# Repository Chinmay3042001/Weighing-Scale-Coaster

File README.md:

# Weighing Scale Coaster

A precision coffee scale built around the HX711 load cell amplifier, optimized for responsiveness and stability. Designed for baristas, tinkerers, and embedded engineers who care about both performance and personality.

## Features
• 	HX711-based load cell interface with high-resolution weight readings

• 	Reference-inspired filtering pipeline adapted from Analog Devices' weigh scale design

• 	OLED display with expressive dome-shaped eyes and smile animation

• 	Timer with short press toggle and long press reset

• 	Flicker-free weight display using hysteresis and trimmed averaging

• 	Designed for both Raspberry Pi Pico W and Seeed Studio XIAO ESP32-C6

## Hardware Overview
### Components
• 	HX711 Load Cell Amplifier

• 	5 kg Load Cell

• 	SSD1306 OLED Display (128×32)

• 	Two momentary push buttons (Tare + Timer) . To be replaced with capacitive touch 

• 	Microcontroller: Raspberry Pi Pico W or Seeed Studio XIAO ESP32-C6

## Wiring Table

| Pin on OLED       | Pin on HX711 | Pin on Pico W | Pin on XIAO ESP32-C6 |
|---------------|--------------|----------------|----------------------|
| VCC           | VCC          | 3.3V           | 3.3V                 |
| GND           | GND          | GND            | GND                  |    
| Data (DT)     | DT           | GPIO 16        | GPIO 10              |
| Clock (SCK)   | SCK          | GPIO 17        | GPIO 11              |
| OLED SDA      | SDA          | GPIO 4         | GPIO 4               |    
| OLED SCL      | SCL          | GPIO 5         | GPIO 5               |
| Tare Button   | -            | GPIO 18        | GPIO 6               |
| Timer Button  | -            | GPIO 19        | GPIO 7               |

## Load Cell Algorithm
This project adapts the signal processing architecture from Analog Devices' weigh scale reference design to the HX711.
Filtering Pipeline

• 	Trimmed Moving Average: Removes min/max outliers from a rolling window to suppress noise while preserving step response.

• 	Step Detection: Detects real weight changes using dual-threshold logic and pre-fills the filter buffer to skip lag.

• 	Display Hysteresis: Prevents flicker by suppressing small changes below a threshold.

### Why It Works
• 	HX711 is a 24-bit sigma-delta ADC with built-in gain and ratiometric measurement.

• 	Filtering compensates for its limited noise-free resolution and slow sample rate.

• 	The result: smooth, stable, and responsive weight readings even with low-cost hardware.

## User Interaction

OLED shows timer and weight. Startup animation includes blinking eyes and a smile. A Hall effect sensor to be integrated for a lid-activated deep sleep and wake mode.

Future Improvements
• 	Calibration helper script for computing 

• 	BLE or Wi-Fi integration for remote brew tracking

• 	Capacitive touch buttons

Credits
Built by Maurice D'Moss, mechanical product design engineer with a passion for coffee and embedded systems.
Filtering architecture inspired by Analog Devices' weigh scale reference design.

## License

This project is licensed under the [Creative Commons Attribution-NonCommercial 4.0 International License](https://creativecommons.org/licenses/by-nc/4.0/).

You are free to use, modify, and share this project for personal and educational purposes.  
Commercial use is not permitted without explicit permission from the author.

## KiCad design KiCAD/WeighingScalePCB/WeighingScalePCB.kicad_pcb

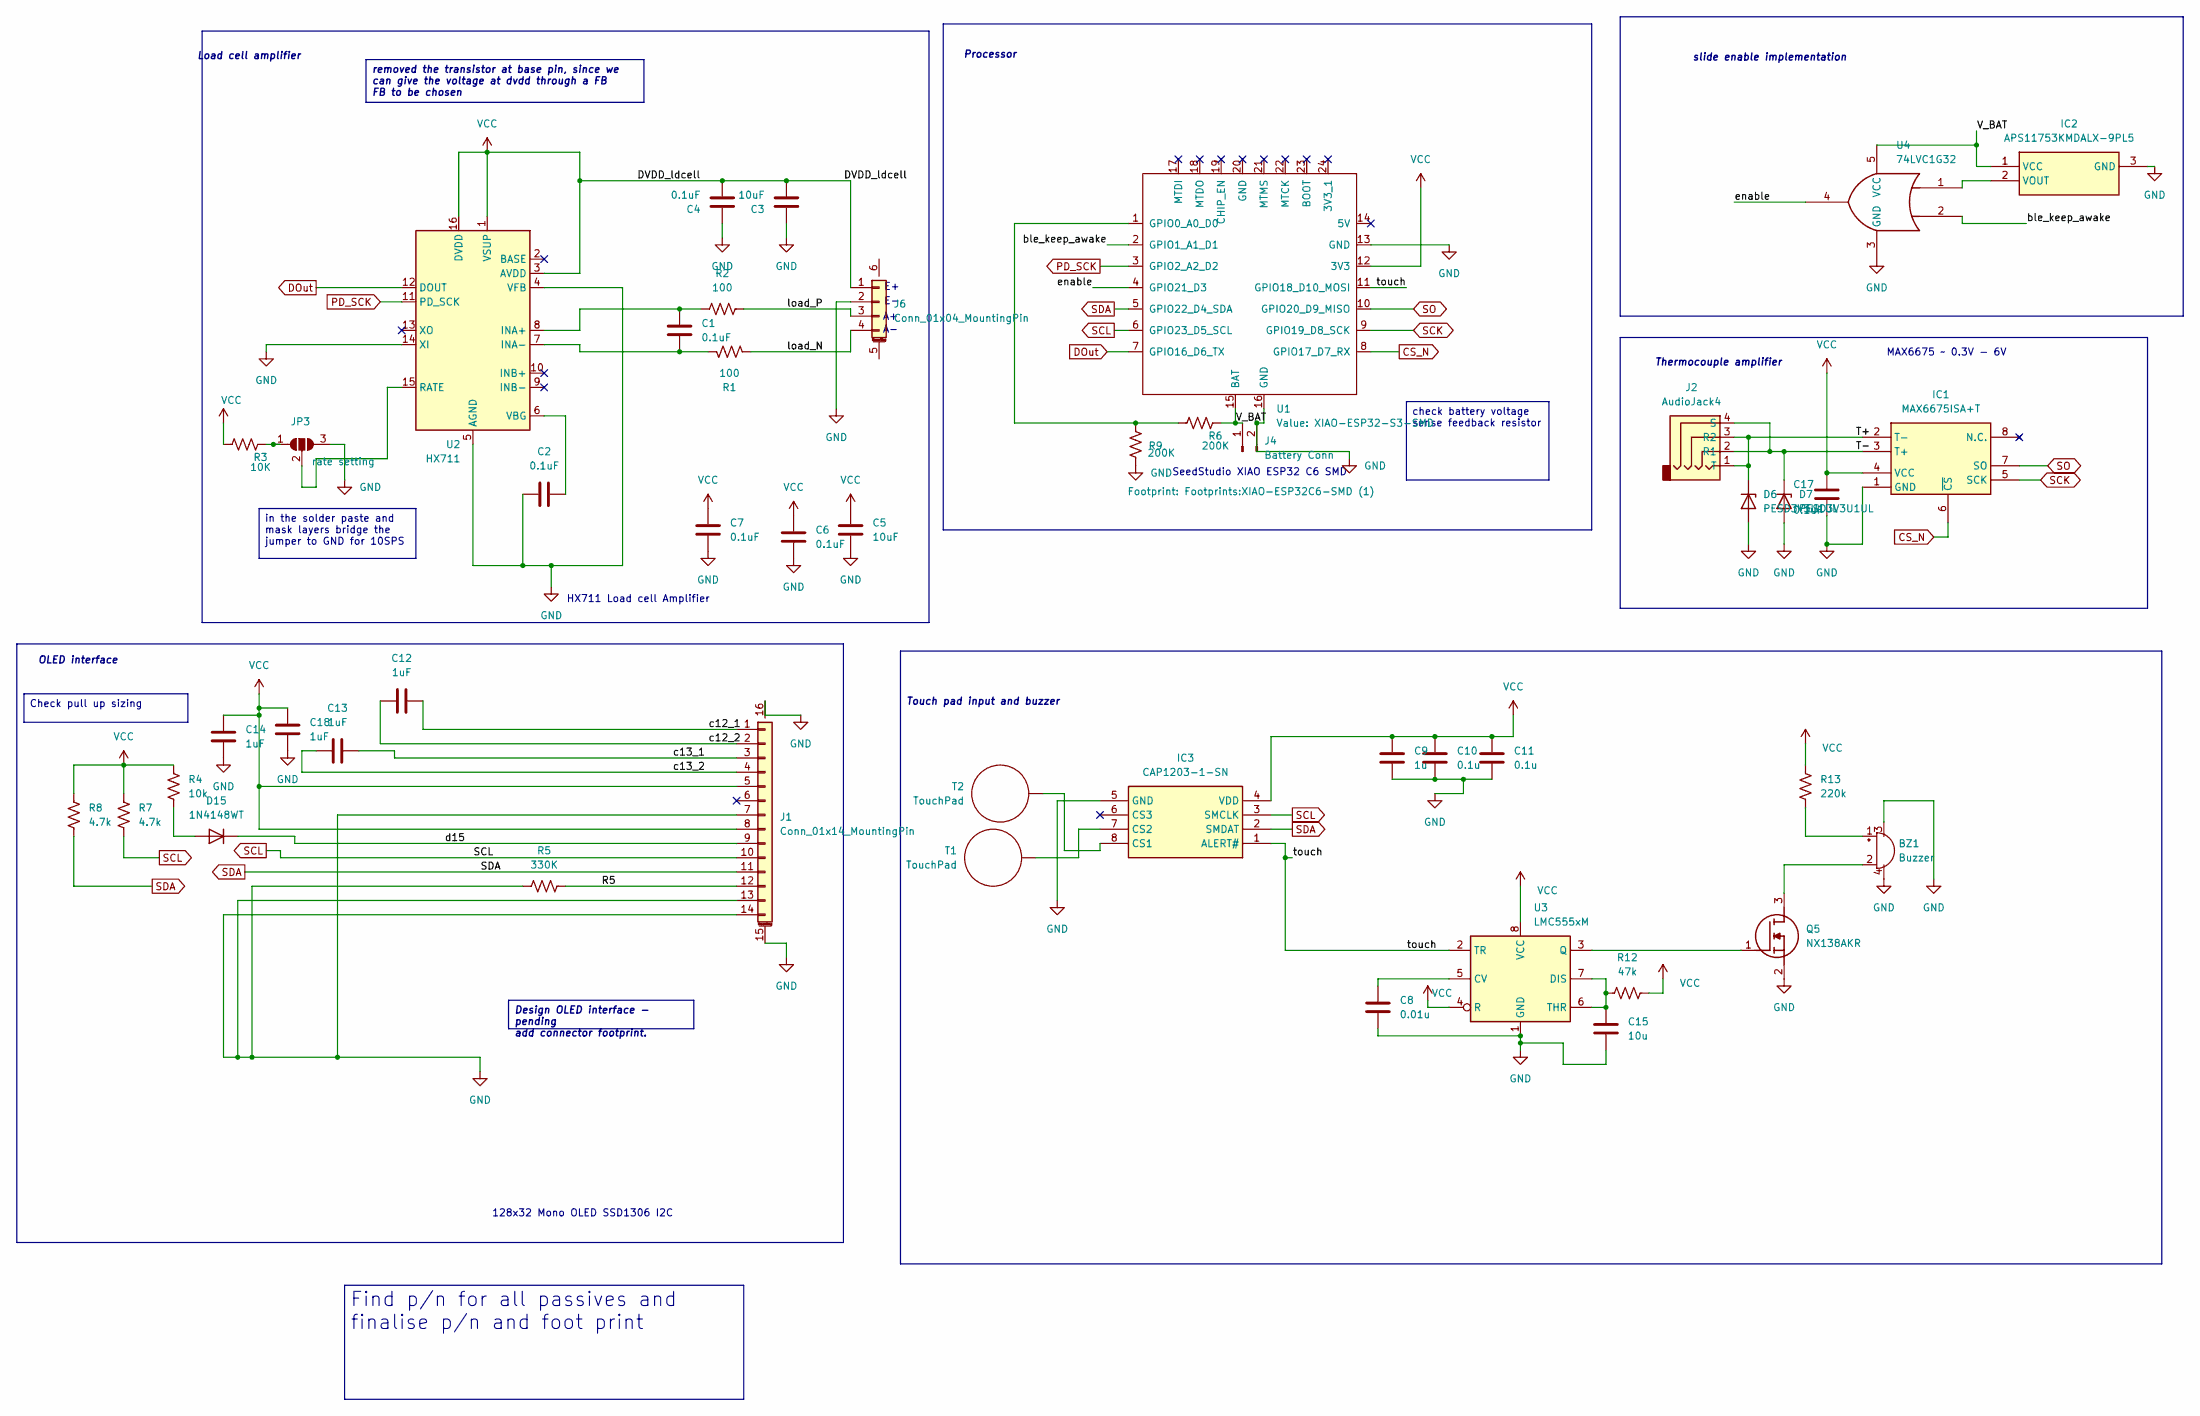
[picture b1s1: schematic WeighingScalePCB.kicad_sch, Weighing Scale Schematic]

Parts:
BZ1: Buzzer; CL7525A_buzzer
C1, C2, C4, C6, C7, C17: 0.1uF; C_0603_1608Metric
C3, C5: 10uF; C_0603_1608Metric
C8: 0.01u; C_0603_1608Metric
C9: 1u; C_0603_1608Metric
C10, C11: 0.1u; C_0603_1608Metric
C12, C13, C14, C18: 1uF; C_0603_1608Metric
C15: 10u; C_0603_1608Metric
D6, D7: PESD3V3U1UL; D_SOD-882
D15: 1N4148WT; D_SOD-523
IC1: MAX6675ISA+T; SOIC127P600X175-8N_MAX6675; Mouser Part Number 700-MAX6675ISAT
IC2: APS11753KMDALX-9PL5; SOT95P240X115-3N_Hall effect; Mouser Part Number 250-APS11753KMD-9PL5
IC3: CAP1203-1-SN; CAP1203_SOIC127P600X175-8N; Mouser Part Number 579-CAP1203-1-SN
J1: Conn_01x14_MountingPin; SFV14R3STBE1HLF_oled_conn
J2: AudioJack4; PRT12639_thermocouple_conn
J4: Battery Conn; PinHeader_2x01_P2.00mm_Vertical_SMD
J6: Conn_01x04_MountingPin; SM04B-SRSS-TB_LFSN_
JP3: rate setting; SolderJumper-3_P1.3mm_Open_RoundedPad1.0x1.5mm
Q5: NX138AKR; SOT95P230X110-3N; Mouser Part Number 771-NX138AKR
R1, R2: 100; R_0603_1608Metric
R3: 10K; R_0603_1608Metric
R4: 10k; R_0402_1005Metric
R5: 330K; R_0402_1005Metric
R6, R9: 200K; R_0603_1608Metric
R7, R8: 4.7k; R_0603_1608Metric
R12: 47k; R_0603_1608Metric
R13: 220k; R_0603_1608Metric
T1: TouchPad; touchpad
T2: TouchPad; touchpad 2
U1: XIAO-ESP32-S3-SMD; XIAO-ESP32C6-SMD (1)
U2: HX711; SOIC-16_3.9x9.9mm_P1.27mm
U3: LMC555xM; SOIC-8_3.9x4.9mm_P1.27mm
U4: 74LVC1G32; SOT95P285X140-5N

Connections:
/R5: J1.12, R5.2
/T+: D6.1 (K), IC1.2 (T-), J2.1 (T), J2.3 (R2)
/T-: D7.1 (K), IC1.3 (T+), J2.2 (R1), J2.4 (S)
/V_BAT: IC2.1 (VCC), J4.1, R6.1, U1.15 (BAT), U4.5 (VCC)
/ble_keep_awake: U1.2 (GPIO1_A1_D1), U4.2
/c12_1: C12.2, J1.1
/c12_2: C12.1, J1.2
/c13_1: C13.2, J1.3
/c13_2: C13.1, J1.4
/d15: D15.1 (K), J1.9
/enable: U1.4 (GPIO21_D3), U4.4
/load_N: J6.4, R1.1
/load_P: J6.3, R2.1
/touch: IC3.1 (ALERT#), U1.11 (GPIO18_D10_MOSI), U3.2 (TR)
CS_N: IC1.6 (~CS), U1.8 (GPIO17_D7_RX)
DOut: U1.7 (GPIO16_D6_TX), U2.12 (DOUT)
GND: BZ1.3 (+), BZ1.4 (+), C2.1, C3.1, C4.1, C5.2, C6.2, C7.2, C8.2, C9.2, C10.2, C11.2, C14.1, C15.2, C17.1, C18.1, D6.2 (A), D7.2 (A), IC1.1 (GND), IC2.3 (GND), IC3.5 (GND), J1.7, J1.13, J1.14, J1.15 (MountPin), J1.16 (MountPin), J4.2, J6.2, JP3.3 (B), Q5.2 (S), R5.1, R9.2, U1.13 (GND), U1.16 (GND), U2.4 (VFB), U2.5 (AGND), U2.14 (XI), U3.1 (GND), U4.3 (GND)
unnamed: BZ1.1 (+), R13.1
unnamed: BZ1.2 (-), Q5.3 (D)
unnamed: D15.2 (A), R4.2
unnamed: IC2.2 (VOUT), U4.1
unnamed: IC3.8 (CS1), T2.T2 (Pad)
unnamed: IC3.7 (CS2), T1.T1 (Pad)
unnamed: JP3.1 (A), R3.1
unnamed: JP3.2 (C), U2.15 (RATE)
unnamed: Q5.1 (G), U3.3 (Q)
unnamed: R6.2, R9.1, U1.1 (GPIO0_A0_D0)
unnamed: C1.1, R2.2, U2.8 (INA+)
unnamed: C1.2, R1.2, U2.7 (INA-)
unnamed: C2.2, U2.6 (VBG)
unnamed: C8.1, U3.5 (CV)
unnamed: C15.1, R12.1, U3.6 (THR), U3.7 (DIS)
PD_SCK: U1.3 (GPIO2_A2_D2), U2.11 (PD_SCK)
SCK: IC1.5 (SCK), U1.9 (GPIO19_D8_SCK)
SCL: IC3.3 (SMCLK), J1.10, R7.2, U1.6 (GPIO23_D5_SCL)
SDA: IC3.2 (SMDAT), J1.11, R8.2, U1.5 (GPIO22_D4_SDA)
SO: IC1.7 (SO), U1.10 (GPIO20_D9_MISO)
VCC: C3.2, C4.2, C5.1, C6.1, C7.1, C9.1, C10.1, C11.1, C14.2, C17.2, C18.2, IC1.4 (VCC), IC3.4 (VDD), J1.5, J1.8, J6.1, R3.2, R4.1, R7.1, R8.1, R12.2, R13.2, U1.12 (3V3), U2.1 (VSUP), U2.3 (AVDD), U2.16 (DVDD), U3.4 (R), U3.8 (VCC)

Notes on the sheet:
HX711 Load cell Amplifier
MAX6675 ~ 0.3V - 6V
slide enable implementation
OLED interface
Load cell amplifier
SeedStudio XIAO ESP32 C6 SMD
Thermocouple amplifier
Touch pad input and buzzer
Processor
128x32 Mono OLED SSD1306 I2C
removed the transistor at base pin, since we can give the voltage at dvdd through a FB FB to be chosen
Find p/n for all passives and finalise p/n and foot print
in the solder paste and mask layers bridge the jumper to GND for 10SPS
Design OLED interface - pending add connector footprint.
check battery voltage sense feedback resistor
Check pull up sizing

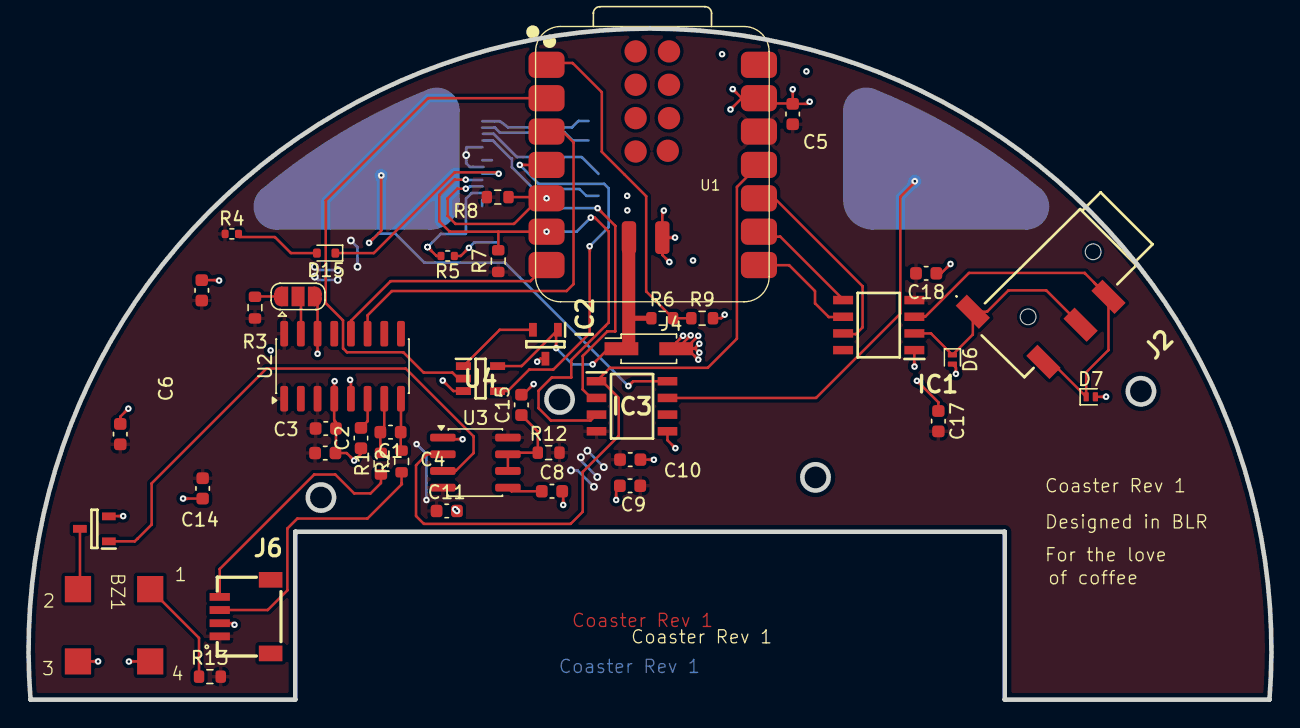
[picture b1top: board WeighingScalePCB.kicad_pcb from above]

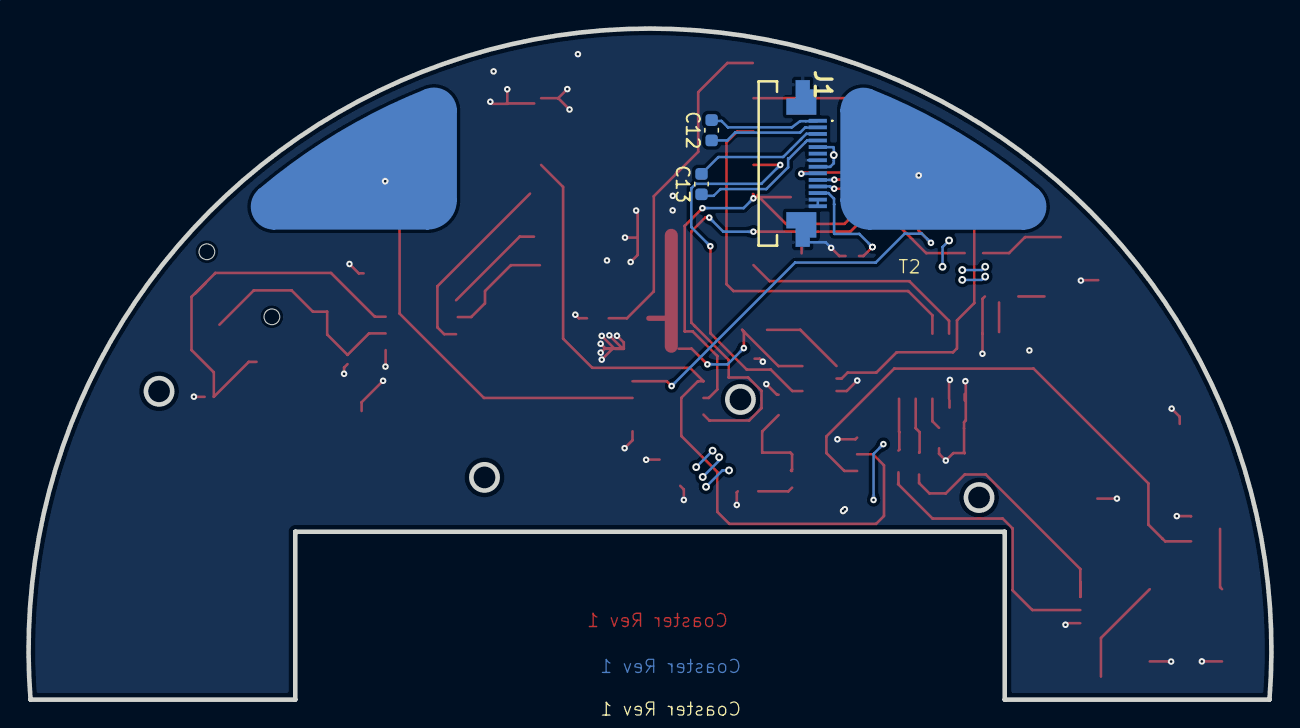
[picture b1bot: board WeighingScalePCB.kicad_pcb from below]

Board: 2 copper layers, 94.6 x 51.1 mm, 47 parts (3 on the bottom side), 38 nets.

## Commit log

2025-10-01 updated connectors, added chip en circuit
2025-10-01 1. Added buzzer beep implementation - to be reviewed and calculations to be finalised 2. cleaned up schematic 3. added comments of pending activities
2025-10-01 Added half millisecond beep
2025-10-02 Added notes for buzzer ckt added design note for hx711
2025-10-02 Test commit
2025-10-02 added trigger implementation for buzzer
2025-10-02 added components to library
2025-10-02 Added touch pad implementation
2025-10-03 replaced ne555 with lmc555 since we are operating at 3.3v
2025-10-03 1. added TOG = 0 and AHLB = 0 for direct mode and active high setting. 2. made all digital ICs LVCMOS
2025-10-04 made all passives 0603, added design notes, added fb between avdd and dvdd in hx711, removed transistor in hx711.
2025-10-05 added DXF pcb shape file
2025-10-05 imported schematic footprints to layout, noted list of missing fp
2025-10-06 Added flowchart for board and dxf in the layout for card edge and placement of components
2025-10-06 added more specific p/n for d flip flop
2025-10-06 Corrected time and tare orring circuit
2025-10-10 assigned footprints
2025-10-10 added toucpad and all fps, only ferrite selection pending
2025-10-18 added gnd plane fixed touch pad footprint, desiganed thermocouple amp, added ttp base ckt
2025-10-27 layout done, decap placement and ferrite bead choice pending
2025-10-27 dvdd for loadcell updated as a pwr pour
2025-10-27 cleared all islands and unconnected GNDs, drc and erc pending, ferrite pending, linked 3d for thermocouple amp, touchpad ic and xiao
2025-10-28 fb removed, decaps will be sufficient, add more decaps, add cap between vbat and vcc
2025-10-30 dxf to be updated, start design verification document next
2025-10-30 all 3d added
2025-10-31 buzzer and J2 3d pending, design doc pending, edge cuts modified to remove redundant area, mounting holes are now m2 compatible
2025-12-10 changed touch sensor to CAP1203, yet to update in layout schematic done.
2025-12-10 added cap to threshold of 555, design 555 timer and simulate with next commit
2026-01-18 DRCs cleared
2026-01-18 gerbers updated
2026-01-18 version added, artwork added, gerber updated accordingly
2026-01-18 rev added in each gerber layer
